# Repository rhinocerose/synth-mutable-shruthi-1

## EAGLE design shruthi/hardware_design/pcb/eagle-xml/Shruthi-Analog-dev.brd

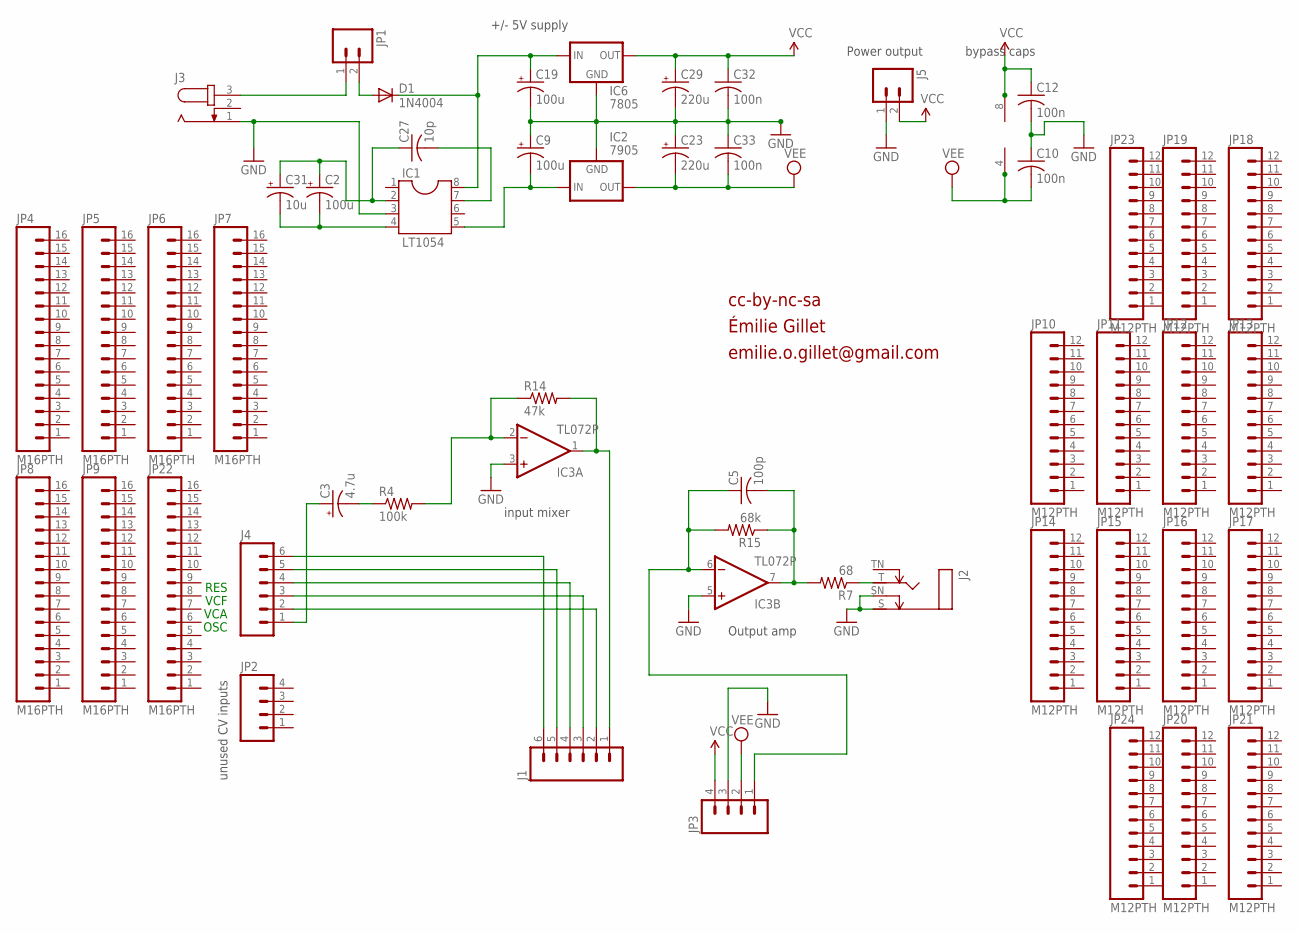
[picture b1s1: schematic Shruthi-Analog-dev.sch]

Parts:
C2: 100u; E2,5-6
C3: 4.7u; E2,5-6
C5: 100p; C025-025X050
C9, C19: 100u; E2,5-7
C10, C12, C32, C33: 100n; C025-025X050
C23, C29: 220u; E5-10,5
C27: 10p; C025-025X050
C31: 10u; E2,5-5
D1: 1N4004; DO41-10
IC1: LT1054; DIL08
IC2: 7905; 79XXS
IC3: TL072P; DIL08
IC6: 7805; 78XXS
J1, J4: M06SIP; 1X06
J2: MONOSWS; NMJ4HC-S
J3: JACK-PLUG; SPC4078_LARGER_HOLES
J5: M02PTH; 1X02
JP1: M02; 1X02_LONGPADS
JP2, JP3: M04PTH; 1X04
JP4, JP5, JP6, JP7, JP8, JP9, JP22: M16PTH; 1X16
JP10, JP11, JP12, JP13, JP14, JP15, JP16, JP17, JP18, JP19, JP20, JP21, JP23, JP24: M12PTH; 1X12
R4: 100k; 0204/7
R7: 68; 0204/7
R14: 47k; 0204/7
R15: 68k; 0204/7

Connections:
GND: C9.+, C10.1, C12.2, C19.-, C23.+, C29.-, C32.2, C33.1, IC1.3, IC2.GND, IC3.3 (+IN), IC3.5 (+IN), IC6.GND, J2.S, J2.SN, J3.1, J5.1, JP3.3
unnamed: C2.+, C27.1, C31.+, IC1.2
unnamed: J1.5, J4.5
unnamed: J3.3, JP1.1
unnamed: C19.+, D1.C, IC1.8, IC6.IN
unnamed: C2.-, C31.-, IC1.4
unnamed: J1.6, J4.6
unnamed: J1.3, J4.3
unnamed: IC3.1 (OUT), J1.1, R14.2
unnamed: C3.+, J4.1
unnamed: C27.2, IC1.7
unnamed: IC3.2 (-IN), R4.2, R14.1
unnamed: C3.-, R4.1
unnamed: J1.2, J4.2
unnamed: J2.T, R7.1
unnamed: J1.4, J4.4
unnamed: C9.-, IC1.5, IC2.IN
unnamed: D1.A, JP1.2
unnamed: C5.2, IC3.7 (OUT), R7.2, R15.1
unnamed: C5.1, IC3.6 (-IN), JP3.1, R15.2
VCC: C12.1, C29.+, C32.1, IC3.8 (V+), IC6.OUT, J5.2, JP3.4
VEE: C10.2, C23.-, C33.2, IC2.OUT, IC3.4 (V-), JP3.2

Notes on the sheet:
Power output
OSC
VCA
VCF
RES
unused CV inputs
input mixer
cc-by-nc-sa
+/- 5V supply
bypass caps
Output amp
Émilie Gillet
emilie.o.gillet@gmail.com

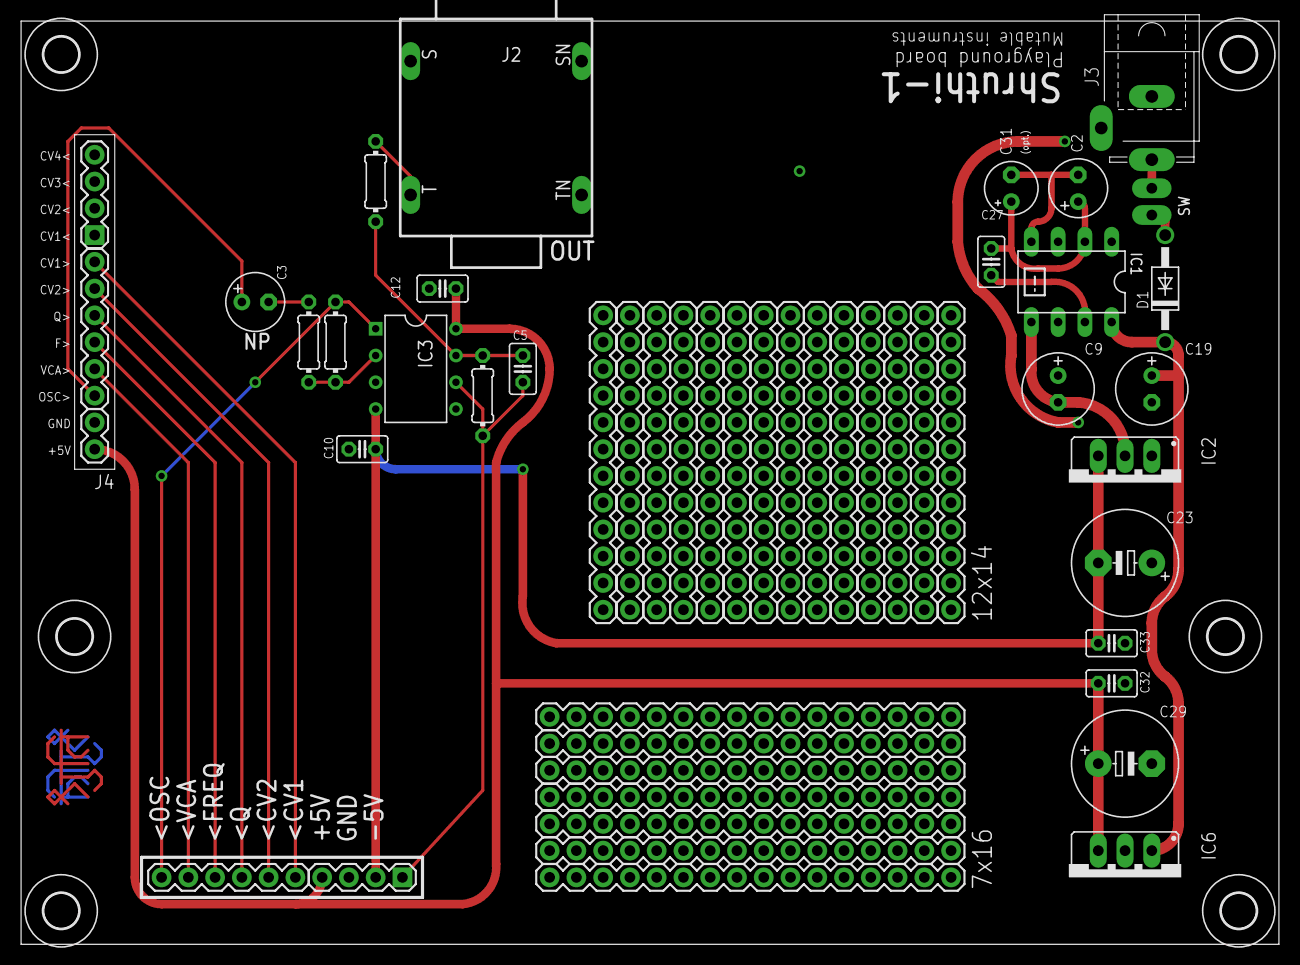
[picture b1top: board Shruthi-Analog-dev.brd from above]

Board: 2 copper layers, 119.4 x 87.6 mm, 57 parts (0 on the bottom side), 22 nets.

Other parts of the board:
U$1, U$2, U$3, U$4, U$5, U$6: 3,3

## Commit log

2025-08-13 Remove .gitmodules (no submodules exist)
2025-08-18 Some changes
